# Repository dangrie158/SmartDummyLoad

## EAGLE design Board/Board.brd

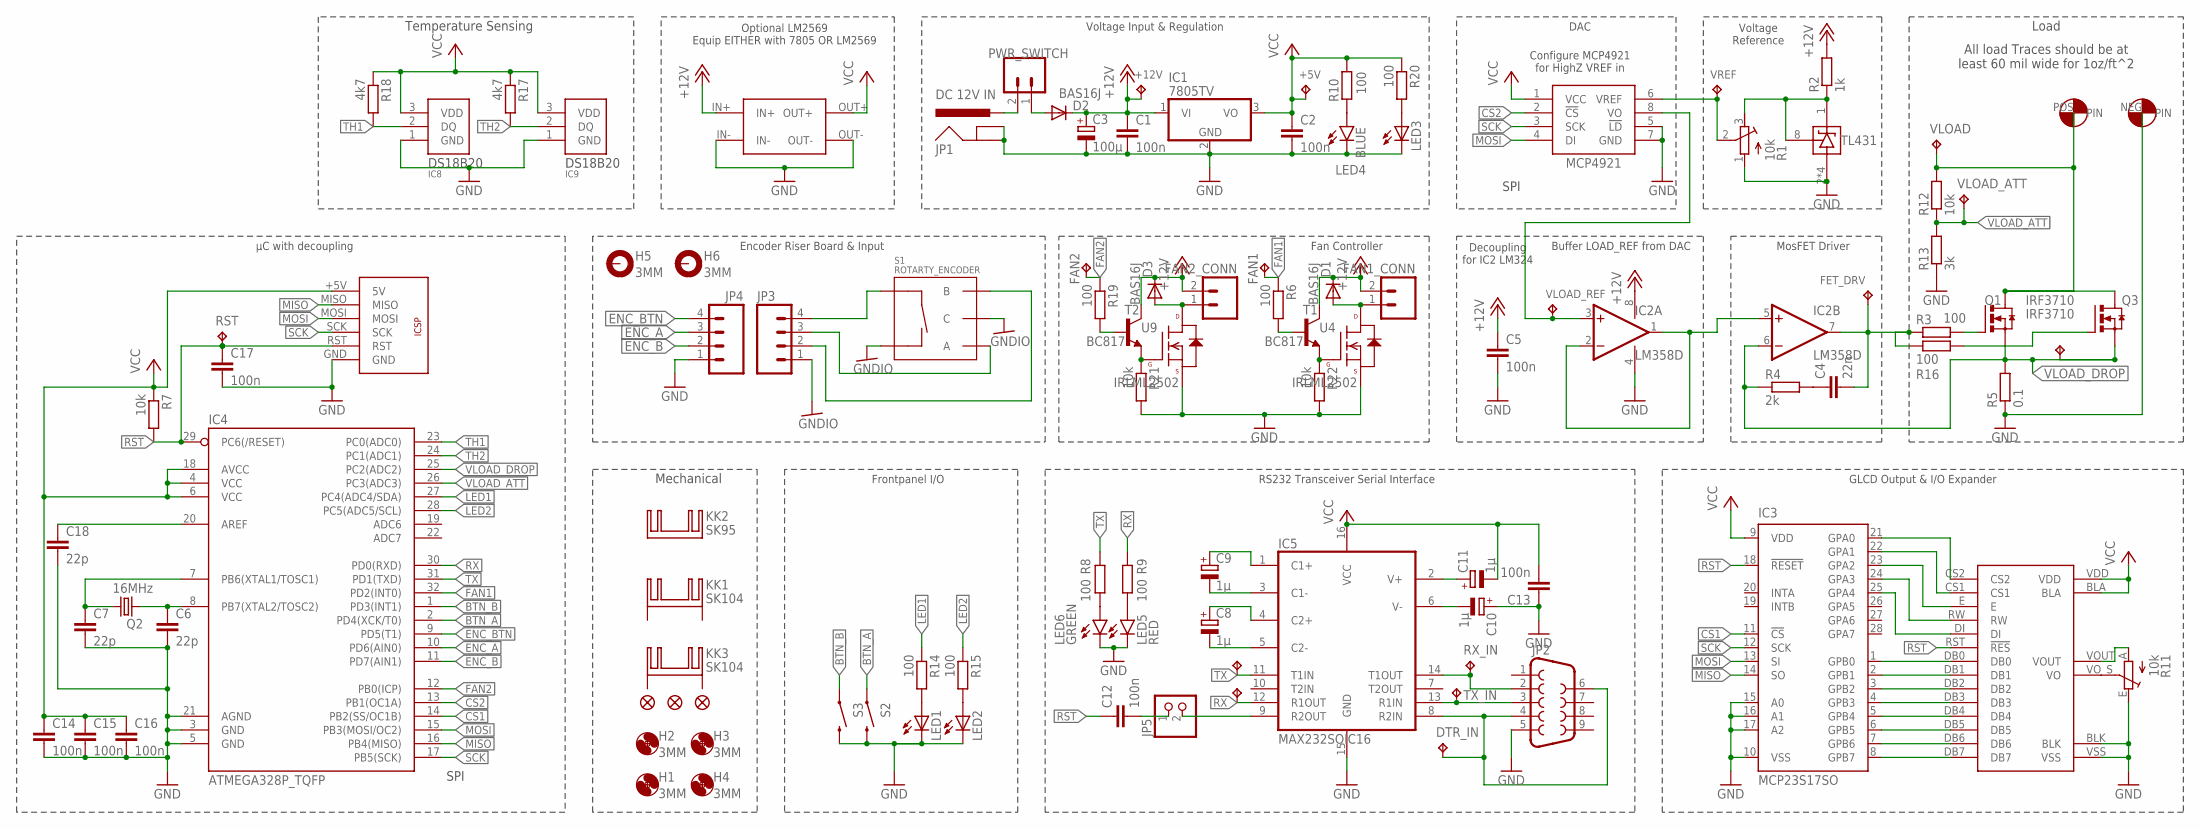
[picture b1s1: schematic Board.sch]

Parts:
+5V, +12V: TPB1,27; B1,27
C1, C2, C5, C12, C13, C14, C15, C16, C17: 100n; C1206K
C3: 100µ; 175TMP-0808
C4: 22n; C1206
C6, C7, C18: 22p; C1206K
C8, C9, C10, C11: 1µ; 153CLV-0405
D1, D2, D3: BAS16J; SOD323-W
DTR_IN: TPB1,27; B1,27
FAN1, FAN2: TPB1,27; B1,27
FAN1_CONN, FAN2_CONN: M02POLAR; MOLEX-1X2
FET_DRV: TPB1,27; B1,27
FID1, FID2, FID3: FIDUCIAL1X2; FIDUCIAL-1X2
H1, H2, H3, H4: 3MM; 3,0
H5, H6: 3MM; 3,0-PAD
IC1: 7805TV; TO220V
IC2: LM358D; SO08
IC3: MCP23S17SO; SO28W
IC4: ATMEGA328P_TQFP; TQFP32-08
IC5: MAX232SOIC16; SO016
IC6: MCP4921; SO-8
IC7: TL431CD; SO-8
IC8, IC9: DS18B20; TO-92
JP1: DC 12V IN; POWER_JACK_PTH
JP2: DB9FEMALE; DB9
JP3, JP4: M04POLAR; MOLEX-1X4
JP5: PINHD-1X2; 1X02
KK1, KK3: SK104; SK104-PAD
KK2: SK95; SK95-2M3
LED1, LED2, LED3: LEDB155; Q62902-B155
LED4: BLUE; LED-0603
LED5: RED; LED-0603
LED6: GREEN; LED-0603
PWR_SWITCH: M02POLAR; MOLEX-1X2
Q1, Q3: IRF3710; TO-220-V
Q2: 16MHz; HC49UP
R1: 10k; RTRIM3296Y
R2: 1k; M1206
R3, R6, R8, R9, R10, R14, R15, R16, R19, R20: 100; R1206
R4: 2k; R1206
R5: 0.1; VTA52
R7, R12, R21, R22: 10k; R1206
R11: 10k; RS3
R13: 3k; R1206
R17, R18: 4k7; M1206
RST: TPB1,27; B1,27
RX: TPB1,27; B1,27
RX_IN: TPB1,27; B1,27
S1: ROTARTY_ENCODER; ROTARY_ENC_PLAIN
S2, S3: SWITCH-MOMENTARY-2SIDE_EZ; TACTILE-PTH-SIDEEZ
T1, T2: BC817; SOT23-BEC
TX: TPB1,27; B1,27
TX_IN: TPB1,27; B1,27
U4, U9: IRLML2502; SOT23-3
U$3: CON-2-HIGAMP; CON-HIGHAMP-0.3"
U$5: ICSPTHROUGHHOLE; ICSP-THROUGHHOLE
U$6: KS0108-GLCDS6B0108; KS0108-S6B0108-GLCD
U$10: LM2569NO_OUTLINE; LM2596_NO_OUTLINE
VLOAD: TPB1,27; B1,27
VLOAD_ATT: TPB1,27; B1,27
VLOAD_DROP: TPB1,27; B1,27
VLOAD_REF: TPB1,27; B1,27
VREF: TPB1,27; B1,27

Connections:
+12V: +12V.TP, C1.1, C3.+, C5.1, D1.C, D2.C, D3.C, FAN1_CONN.2, FAN2_CONN.2, IC1.1 (VI), IC2.8 (V+), R2.2, T1.C, T2.C, U$10.IN+
BTN_A: IC4.2 (PD4(XCK/T0)), S2.1
BTN_B: IC4.1 (PD3(INT1)), S3.1
CS1: IC3.11 (!CS), IC4.14 (PB2(SS/OC1B))
CS2: IC4.13 (PB1(OC1A)), IC6.2 (!CS!)
ENC_A: IC4.10 (PD6(AIN0)), JP4.3
ENC_B: IC4.11 (PD7(AIN1)), JP4.2
ENC_BTN: IC4.9 (PD5(T1)), JP4.4
FAN1: FAN1.TP, IC4.32 (PD2(INT0)), R6.1
FAN2: FAN2.TP, IC4.12 (PB0(ICP)), R19.1
GND: C1.2, C2.2, C3.-, C5.2, C6.2, C7.2, C10.+, C13.1, C14.2, C15.2, C16.2, C17.2, C18.2, IC1.2 (GND), IC2.4 (V-), IC3.10 (VSS), IC3.15 (A0), IC3.16 (A1), IC3.17 (A2), IC4.3 (GND), IC4.5 (GND), IC4.21 (AGND), IC5.15 (GND), IC6.5 (!LD!), IC6.7 (GND), IC7.2 (ANODE), IC7.3 (ANODE), IC7.6 (ANODE), IC7.7 (ANODE), IC8.1 (GND), IC9.1 (GND), JP1.GND, JP1.GNDBREAK, JP2.5, JP4.1, LED1.K (C), LED2.K (C), LED3.K (C), LED4.C, LED5.C, LED6.C, R1.1 (A), R5.1, R11.E, R13.1, R21.2, R22.2, S2.2, S3.2, U4.2 (S), U9.2 (S), U$3.NEG, U$5.GND, U$6.BLK, U$6.VSS, U$10.IN-, U$10.OUT-
GNDIO: JP3.1, S1.C, S1.SW-
LED1: IC4.27 (PC4(ADC4/SDA)), R14.1
LED2: IC4.28 (PC5(ADC5/SCL)), R15.1
LOAD+: Q1.2 (D), Q3.2 (D), R12.2, U$3.POS, VLOAD.TP
MISO: IC3.14 (SO), IC4.16 (PB4(MISO)), U$5.MISO
MOSI: IC3.13 (SI), IC4.15 (PB3(MOSI/OC2)), IC6.4 (DI), U$5.MOSI
unnamed: IC7.1 (CATHODE), IC7.8 (REF), R1.3 (E), R2.1
unnamed: IC6.6 (VREF), R1.2 (S), VREF.TP
unnamed: C4.1, R4.2
unnamed: R22.1, T1.E, U4.1 (G)
unnamed: D1.A, FAN1_CONN.1, U4.3 (D)
unnamed: Q1.1 (G), R3.2
unnamed: IC5.9 (R2OUT), JP5.2
unnamed: R6.2, T1.B
unnamed: C7.1, IC4.7 (PB6(XTAL1/TOSC1)), Q2.1
unnamed: C4.2, FET_DRV.TP, IC2.7 (OUT), R3.1, R16.1
unnamed: C6.1, IC4.8 (PB7(XTAL2/TOSC2)), Q2.2
unnamed: DTR_IN.TP, IC5.8 (R2IN), JP2.4, JP2.6
unnamed: IC5.14 (T1OUT), JP2.2, RX_IN.TP
unnamed: IC5.13 (R1IN), JP2.3, TX_IN.TP
unnamed: C9.-, IC5.3 (C1-)
unnamed: C9.+, IC5.1 (C1+)
unnamed: C8.-, IC5.5 (C2-)
unnamed: C8.+, IC5.4 (C2+)
unnamed: C11.+, IC5.2 (V+)
unnamed: LED4.A, R10.2
unnamed: C10.-, IC5.6 (V-)
unnamed: LED6.A, R8.2
unnamed: LED5.A, R9.2
unnamed: R11.S, U$6.VO
unnamed: R11.A, U$6.VOUT
unnamed: JP1.PWR, PWR_SWITCH.2
unnamed: IC3.1 (GPB0), U$6.DB0
unnamed: IC3.2 (GPB1), U$6.DB1
unnamed: IC3.3 (GPB2), U$6.DB2
unnamed: IC3.4 (GPB3), U$6.DB3
unnamed: IC3.5 (GPB4), U$6.DB4
unnamed: IC3.6 (GPB5), U$6.DB5
unnamed: IC3.7 (GPB6), U$6.DB6
unnamed: IC3.8 (GPB7), U$6.DB7
unnamed: IC3.21 (GPA0), U$6.CS2
unnamed: IC3.22 (GPA1), U$6.CS1
unnamed: IC3.23 (GPA2), U$6.E
unnamed: IC3.24 (GPA3), U$6.RW
unnamed: IC3.25 (GPA4), U$6.DI
unnamed: C18.1, IC4.20 (AREF)
unnamed: D2.A, PWR_SWITCH.1
unnamed: R21.1, T2.E, U9.1 (G)
unnamed: LED1.A, R14.2
unnamed: LED2.A, R15.2
unnamed: JP3.4, S1.SW+
unnamed: JP3.3, S1.A
unnamed: Q3.1 (G), R16.2
unnamed: R19.2, T2.B
unnamed: JP3.2, S1.B
unnamed: D3.A, FAN2_CONN.1, U9.3 (D)
unnamed: LED3.A, R20.2
RST: C12.1, C17.1, IC3.18 (!RESET), IC4.29 (PC6(/RESET)), R7.2, RST.TP, U$5.RST, U$6.RST (!RES!)
RST_EN: C12.2, JP5.1
RX: IC4.30 (PD0(RXD)), IC5.12 (R1OUT), R9.1, RX.TP
SCK: IC3.12 (SCK), IC4.17 (PB5(SCK)), IC6.3 (SCK), U$5.SCK
TH1: IC4.23 (PC0(ADC0)), IC8.2 (DQ), R18.2
TH2: IC4.24 (PC1(ADC1)), IC9.2 (DQ), R17.2
TX: IC4.31 (PD1(TXD)), IC5.11 (T1IN), R8.1, TX.TP
VCC: +5V.TP, C2.1, C11.-, C13.2, C14.1, C15.1, C16.1, IC1.3 (VO), IC3.9 (VDD), IC4.4 (VCC), IC4.6 (VCC), IC4.18 (AVCC), IC5.16 (VCC), IC6.1 (VCC), IC8.3 (VDD), IC9.3 (VDD), R7.1, R10.1, R17.1, R18.1, R20.1, U$5.+5V (5V), U$6.BLA, U$6.VDD, U$10.OUT+
VLOAD_ATT: IC4.26 (PC3(ADC3)), R12.1, R13.2, VLOAD_ATT.TP
VLOAD_DROP: IC2.6 (-IN), IC4.25 (PC2(ADC2)), Q1.3 (S), Q3.3 (S), R4.1, R5.2, VLOAD_DROP.TP
VLOAD_REF: IC2.3 (+IN), IC6.8 (VO), VLOAD_REF.TP
VREF_BUF: IC2.1 (OUT), IC2.2 (-IN), IC2.5 (+IN)

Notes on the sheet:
Buffer LOAD_REF from DAC
Decoupling for IC2 LM324
MosFET Driver
Load
Voltage Reference
DAC
Voltage Input & Regulation
Mechanical
Fan Controller
All load Traces should be at least 60 mil wide for 1oz/ft^2
SPI
Configure MCP4921 for HighZ VREF in
Encoder Riser Board & Input
GLCD Output & I/O Expander
RS232 Transceiver Serial Interface
Optional LM2569 Equip EITHER with 7805 OR LM2569
Temperature Sensing
Frontpanel I/O
µC with decoupling

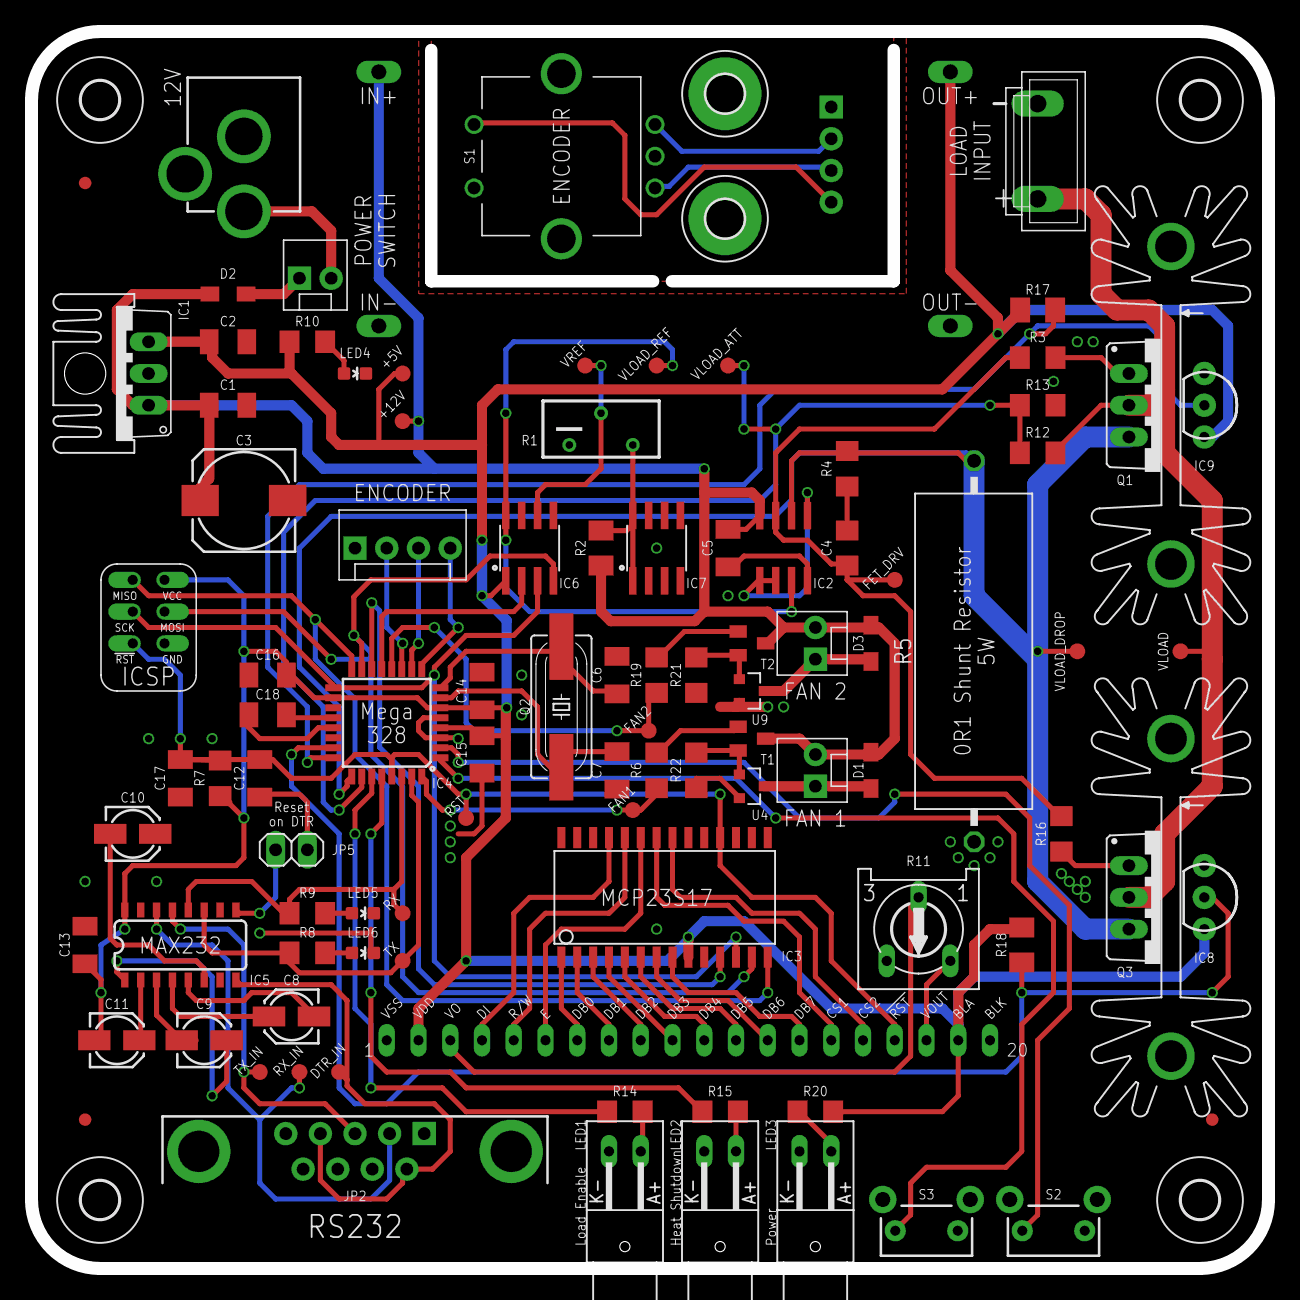
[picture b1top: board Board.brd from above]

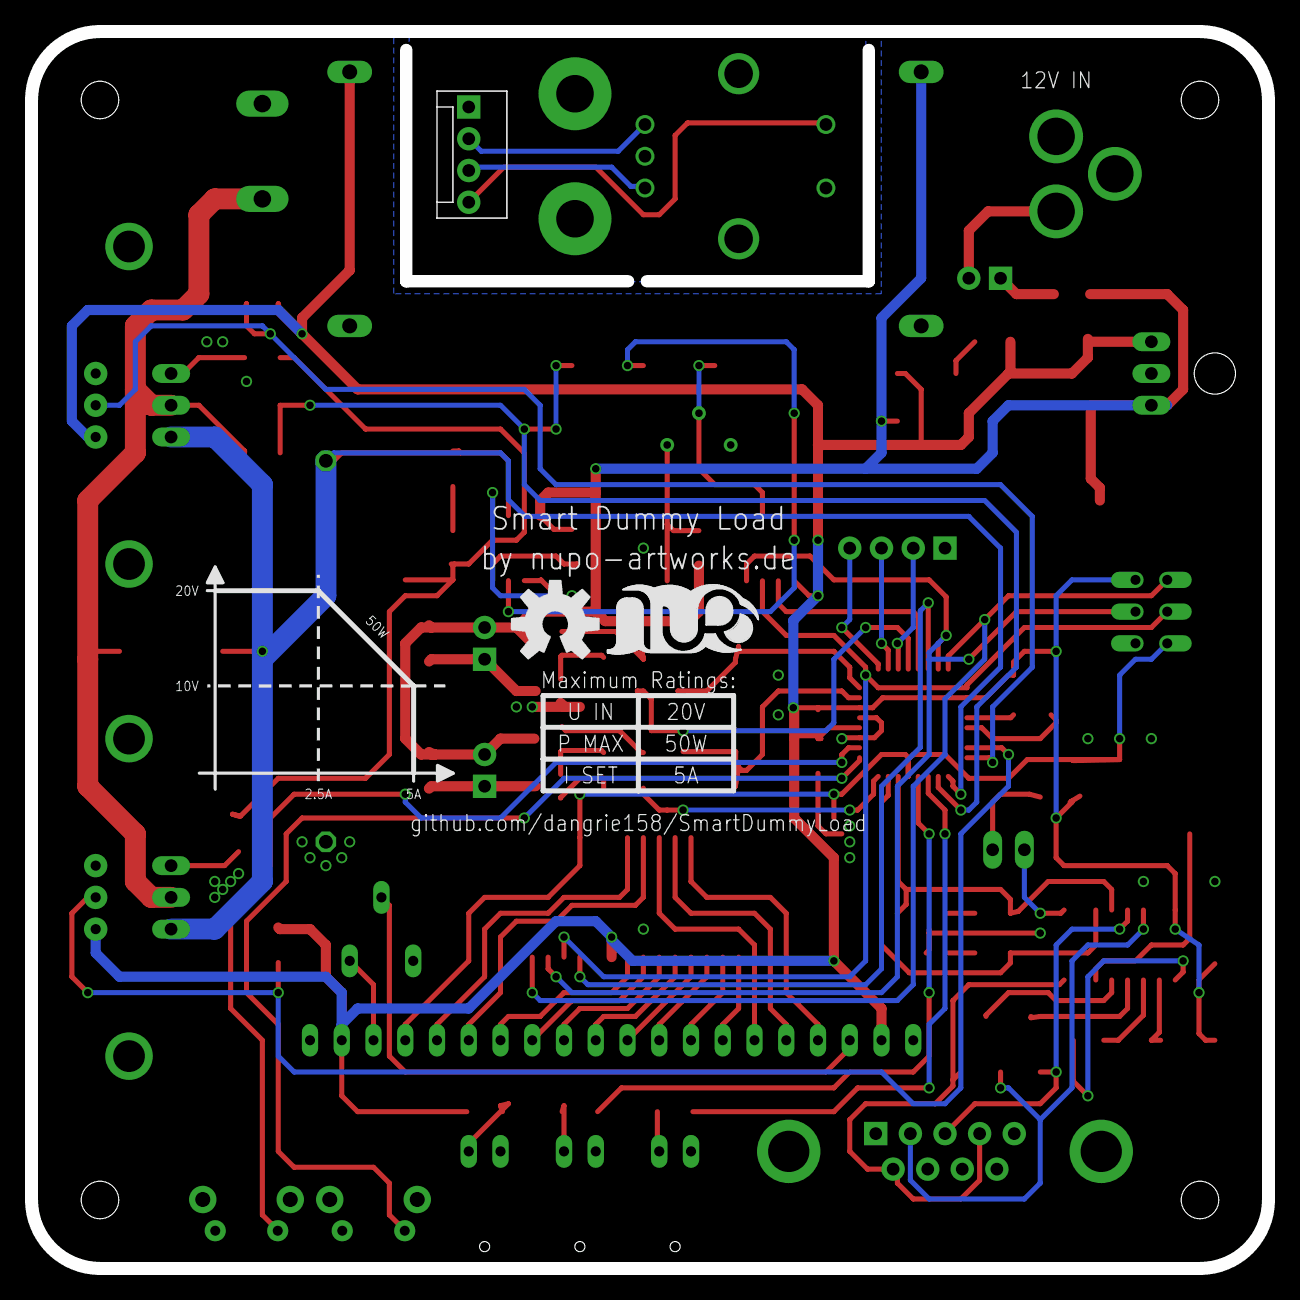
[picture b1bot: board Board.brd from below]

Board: 2 copper layers, 99.0 x 99.0 mm, 110 parts (3 on the bottom side), 80 nets.

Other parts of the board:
U$1: LOGO-SILKSCREEN
U$2: OSHW-LOGO-L

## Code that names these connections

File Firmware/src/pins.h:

// The chip select pin for the MCP4921 DAC
#define CS_DAC 9

// the chip select pin for the MCP23S17 GPIO expander
#define CS_GPIO 10

#define FAN1 2
#define FAN2 8

#define TEMP_SENS1 A0
#define TEMP_SENS2 A1

#define LED1 A4
#define LED2 A5

#define BUTTON_A 4
#define BUTTON_B 3
#define ENC_A 6
#define ENC_B 7
#define ENC_BTN 5

#define VLOAD A3
#define ILOAD A2

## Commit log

2016-03-09 Initial Commit
    This Initial Commit adds the Basic Schematic in the first Version
2016-03-12 Added second MosFET Stage and Temperature Sensing
2016-03-12 routed first version of the board
2016-03-12 added second fan controller
2016-03-12 Routed more of the Board, added an optional LM2569 Module
2016-03-13 worked on silkscreen for passives
2016-03-13 added silkscreen information to bottom
2016-03-13 added fiducials to the board
2016-03-20 added documentation to bottom of board
2016-03-20 refactored project structure
2016-03-20 renamed Board Files in preparation for Exporting PDFs
2016-03-20 added PDFs for the Board and Schematic
2016-04-16 added pull downs to fan drver gates
2016-04-17 lowered decoupling capacitance for VREF to allow fast switching of references
2016-04-24 Added Firmware Objects for all Hardware Interfaces
2016-04-24 switched to platform.io
2016-04-26 removed custom lib ClickEncoder and switched to platfomio provided one
2016-04-26 renamed main ino file to cpp
2016-04-28 added read functions to MCP23S17 lib
2016-04-28 added first version of working GLCD Lib and IO Mapping for MCP23S17
2016-04-29 added sample native mapping for GLCD Lib
2016-04-29 added writing capabilites over a page boundary to GLCD lib
2016-04-29 added graphics functions to GLCD lib
2016-04-29 added Bitmap drawing capability to glcd lib
2016-04-29 removed fonts from GLCD library
2016-04-29 fixed conflicting declaration of fonts
2016-04-29 added guards to avoid redefinition to headers
2016-04-30 removed uneccesary wordWrites in MCP23S17 lib
2016-04-30 improved performace of MCP IO mapping due to caching
2016-04-30 removed uneccecary controler disable calls
2016-04-30 added Progressbar Widget
2016-04-30 fixed off page writing of data for GLCD
2016-05-01 fixed off page writing for GLCD lib
2016-05-01 improved progressbar lib performance with direct page writing
2016-06-07 split out source path of the driving MosFETs
2016-06-15 moved entire charset of Font6x8 a pixel down
2016-06-15 fixed wrong chipset orientation with new LCD
2016-06-15 added functions to asynchronously request the temperature from DS18B20 sensors
2016-06-15 added clamping to Progressbar MAX_VALUE instead of ignoring the set
2016-06-15 added Symbol Font
2016-06-15 cleaned up main code and added header file for main application
2016-06-15 added enclosure design files
2018-09-24 updated firmware

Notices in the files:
parts and their libraries:
SparkFun-Connectors: Licensing: Creative Commons ShareAlike 4.0 International - https://creativecommons.org/licenses/by-sa/4.0
